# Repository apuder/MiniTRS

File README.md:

# MiniTRS

TBD

### Credits

* <a href="https://github.com/shaeberling/mini-trs">mini-trs</a> by Sascha H&auml;berling
* [Micro Model III](https://www.teamten.com/lawrence/projects/micro-model-3/) by Lawrence Kesteloot

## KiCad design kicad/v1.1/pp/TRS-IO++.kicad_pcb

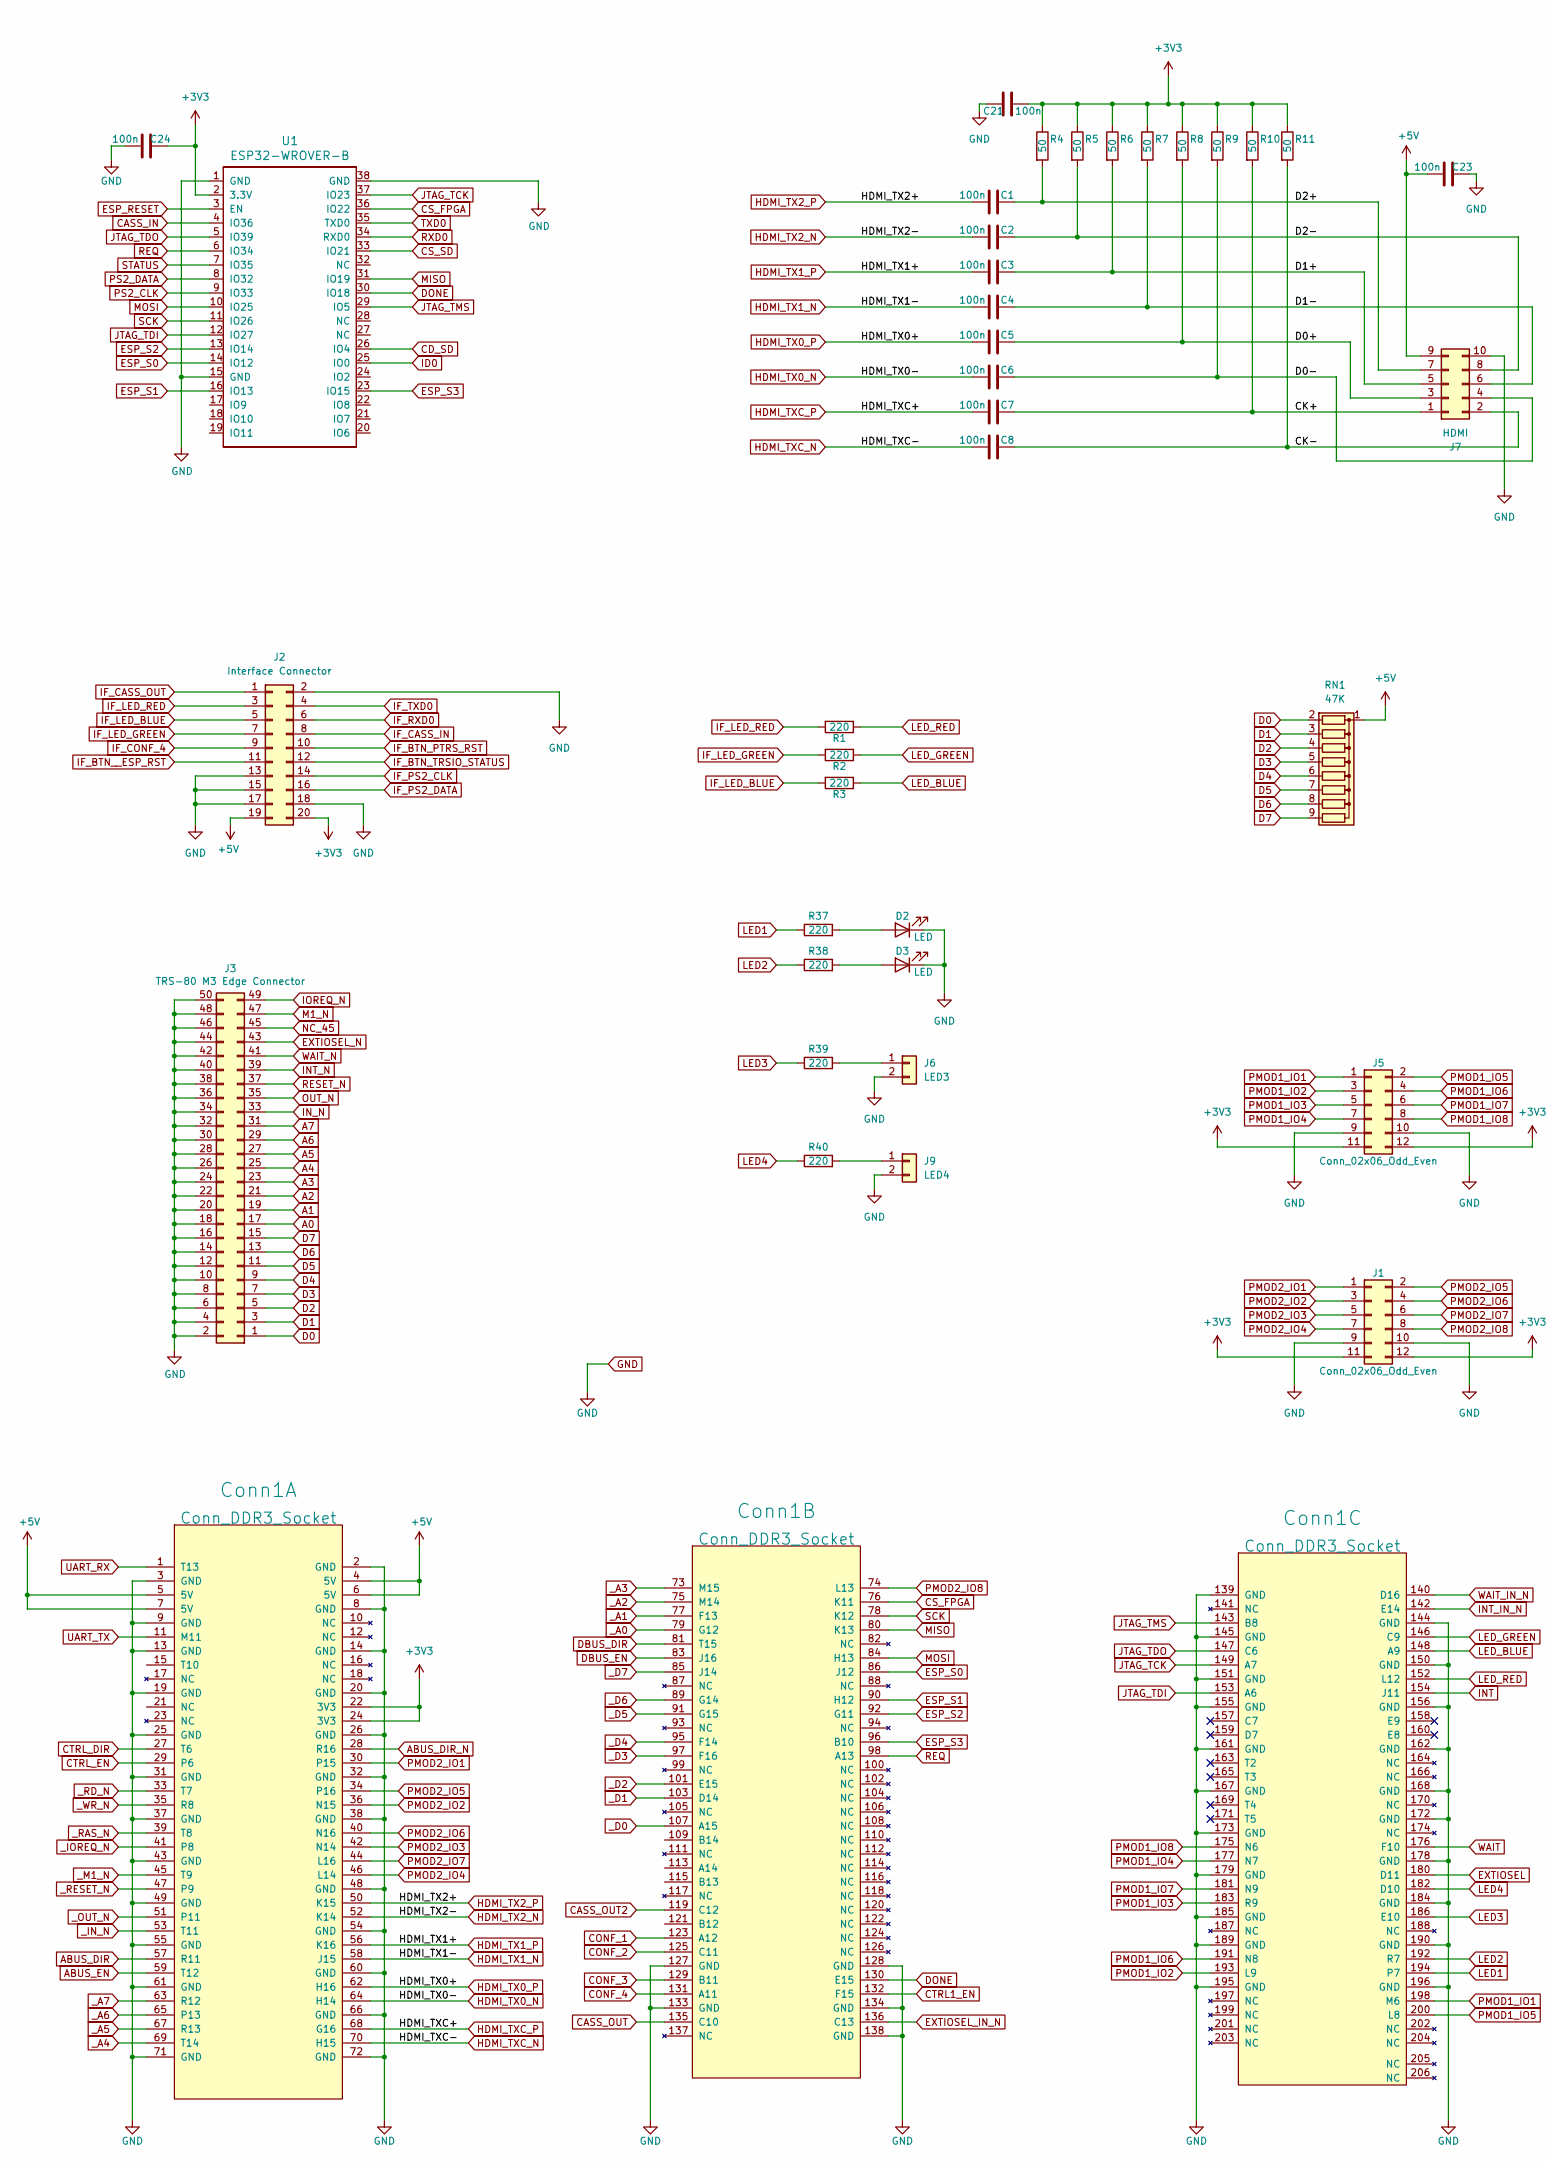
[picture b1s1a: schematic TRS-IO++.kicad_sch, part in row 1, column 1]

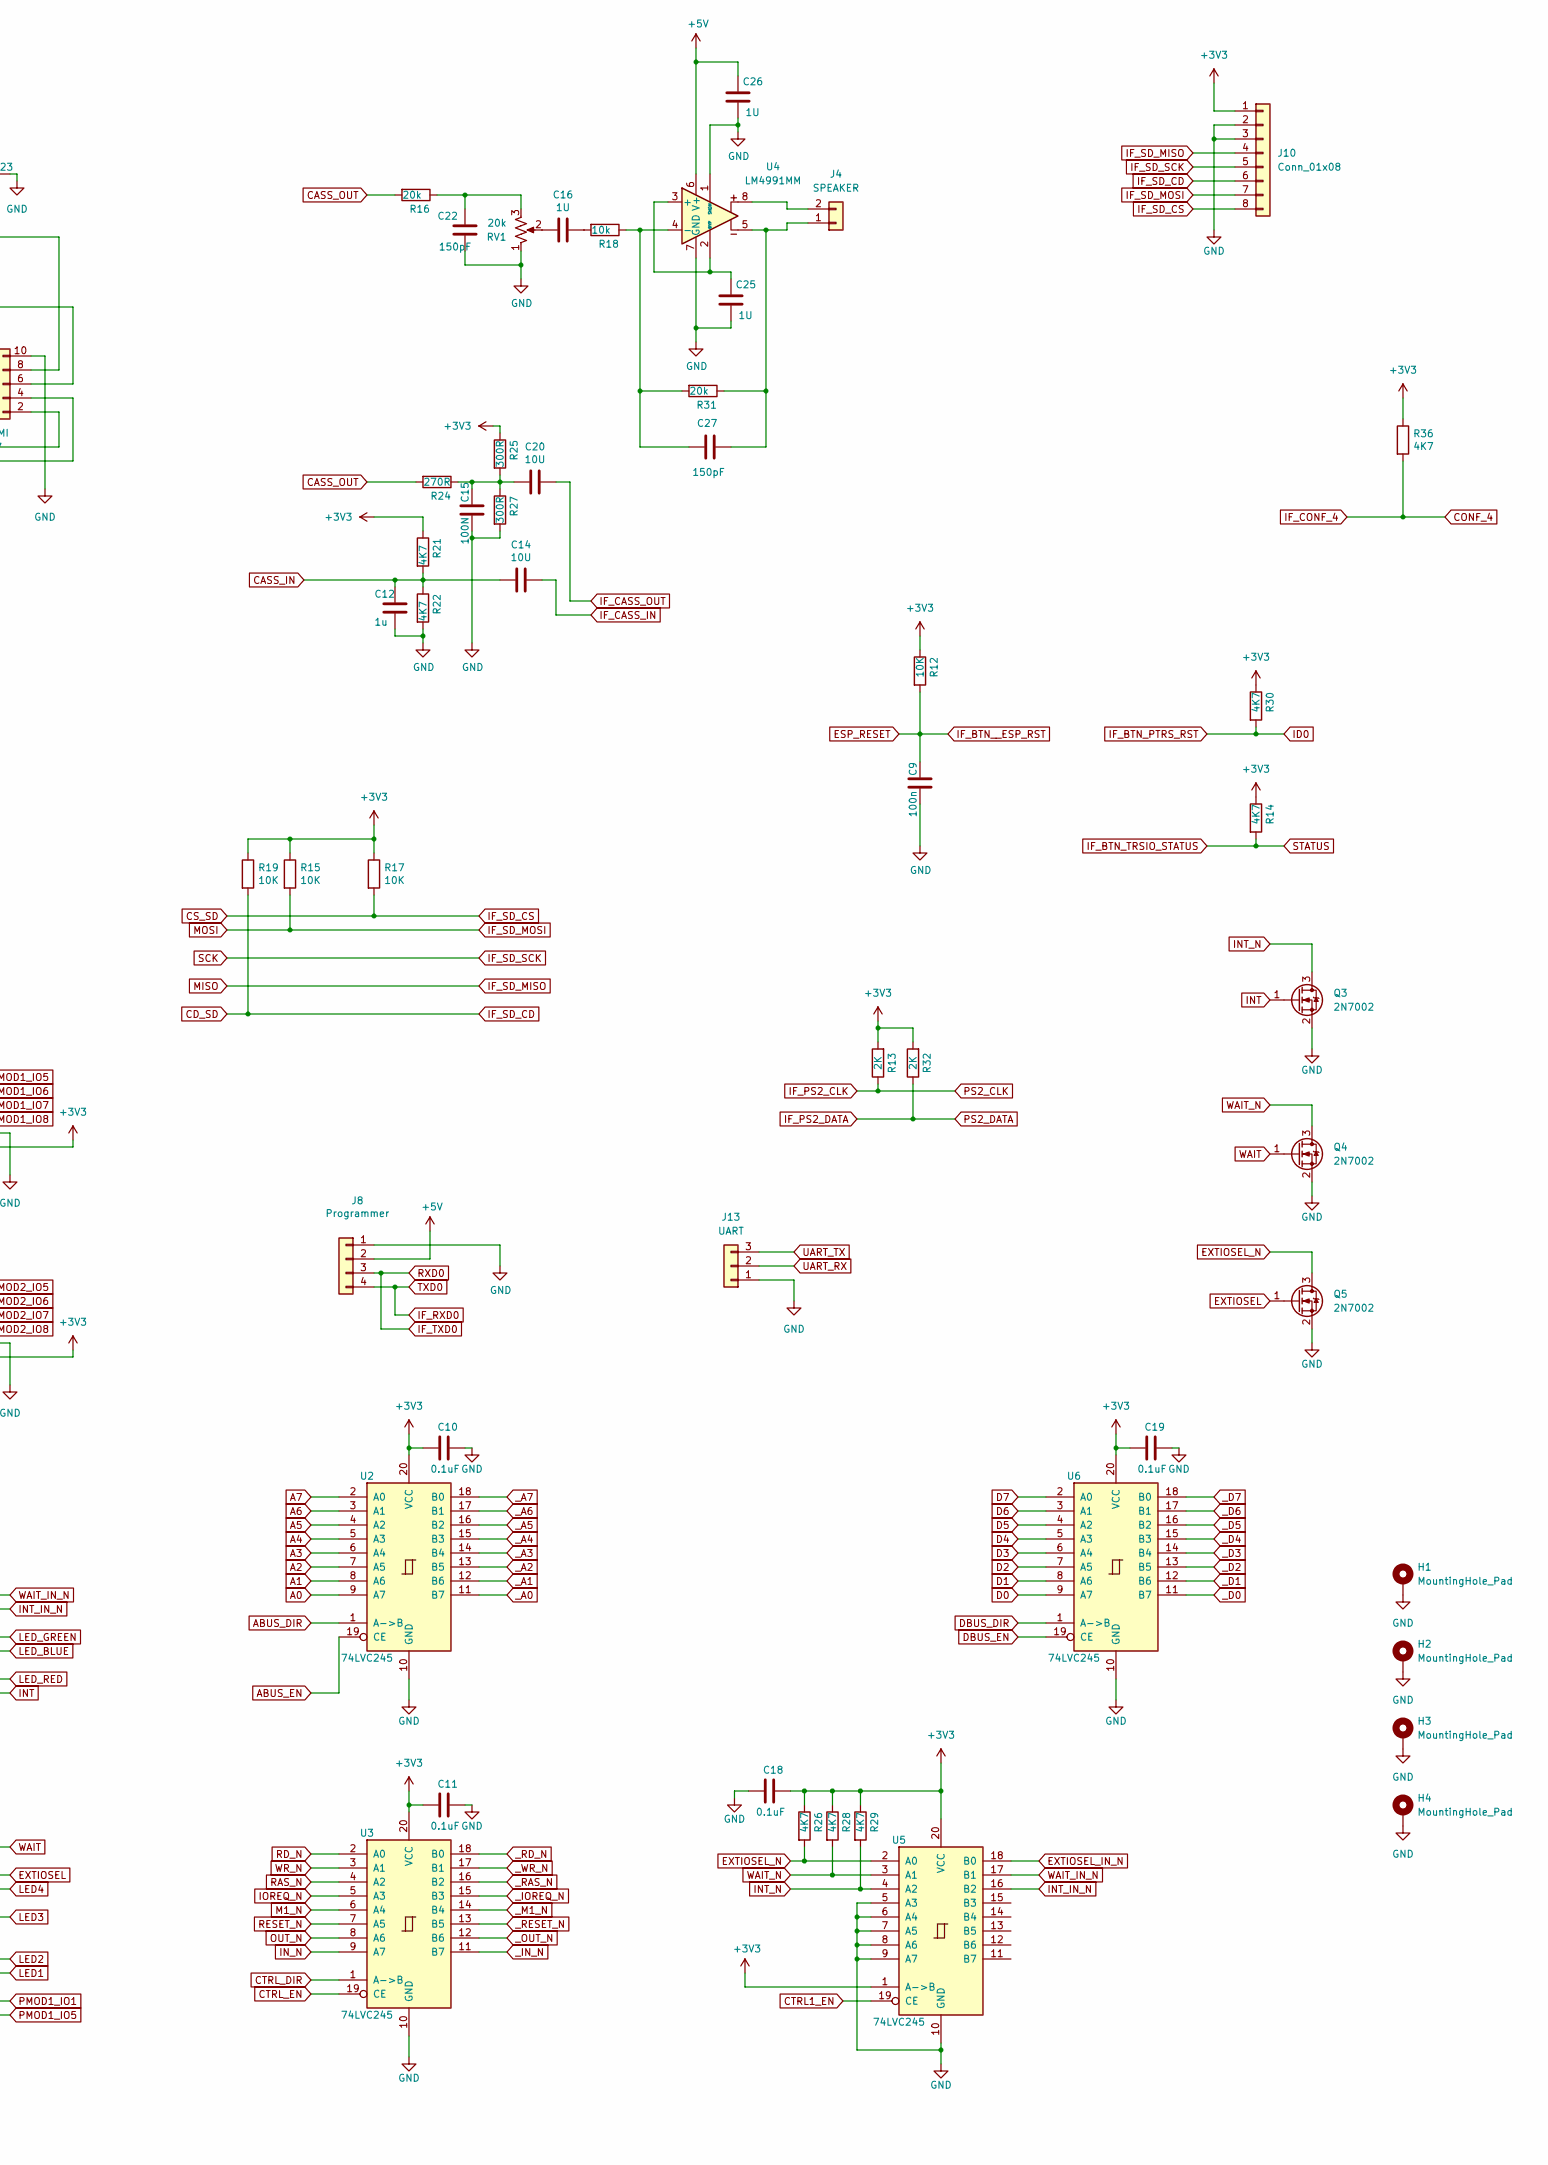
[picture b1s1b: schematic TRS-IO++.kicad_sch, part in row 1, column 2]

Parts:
C1, C2, C3, C4, C5, C6, C7, C8, C9, C21, C23, C24: 100n; C_0805_2012Metric_Pad1.18x1.45mm_HandSolder
C10, C11, C18, C19: 0.1uF; C_0805_2012Metric_Pad1.18x1.45mm_HandSolder
C12: 1u; C_1206_3216Metric_Pad1.33x1.80mm_HandSolder
C14, C20: 10U; C_1206_3216Metric_Pad1.33x1.80mm_HandSolder
C15: 100N; C_0805_2012Metric_Pad1.18x1.45mm_HandSolder
C16, C25, C26: 1U; C_0805_2012Metric_Pad1.18x1.45mm_HandSolder
C22, C27: 150pF; C_0805_2012Metric_Pad1.18x1.45mm_HandSolder
Conn1: Conn_DDR3_Socket; DDR3_socket; LCSC C306045
D2: LED; LED_0805_2012Metric_Pad1.15x1.40mm_HandSolder; LCSC C84256
D3: LED; LED_0805_2012Metric_Pad1.15x1.40mm_HandSolder
H1, H2, H3, H4: MountingHole_Pad; MountingHole_3mm_Pad_Via
J1, J5: Conn_02x06_Odd_Even; PinSocket_2x06_P2.54mm_Vertical; LCSC C358728
J2: Interface Connector; PinHeader_2x10_P1.27mm_Vertical; LCSC C3324132
J3: TRS-80 M3 Edge Connector; EDGE50
J4: SPEAKER; PinHeader_1x02_P2.54mm_Horizontal; LCSC C492410
J6: LED3; PinHeader_1x02_P2.54mm_Vertical; LCSC C225477
J7: HDMI; PinHeader_2x05_P1.27mm_Vertical_SMD; LCSC C598540
J8: Programmer; PinHeader_1x04_P2.54mm_Vertical; LCSC C2691448
J9: LED4; PinHeader_1x02_P2.54mm_Vertical; LCSC C225477
J10: Conn_01x08; PinHeader_1x08_P2.54mm_Vertical
J13: UART; PinHeader_1x03_P2.54mm_Vertical; LCSC C2937625
Q3, Q4, Q5: 2N7002; SOT-23
R1, R2, R3, R37, R38, R39, R40: 220; R_0805_2012Metric_Pad1.20x1.40mm_HandSolder
R4, R5, R6, R7, R8, R9, R10, R11: 50; R_0805_2012Metric_Pad1.20x1.40mm_HandSolder
R12, R15, R17, R19: 10K; R_0805_2012Metric_Pad1.20x1.40mm_HandSolder
R13, R32: 2K; R_0805_2012Metric_Pad1.20x1.40mm_HandSolder
R14, R21, R22, R26, R28, R29, R30, R36: 4K7; R_0805_2012Metric_Pad1.20x1.40mm_HandSolder
R16, R31: 20k; R_0805_2012Metric_Pad1.20x1.40mm_HandSolder
R18: 10k; R_0805_2012Metric_Pad1.20x1.40mm_HandSolder
R24: 270R; R_0805_2012Metric_Pad1.20x1.40mm_HandSolder
R25, R27: 300R; R_0805_2012Metric_Pad1.20x1.40mm_HandSolder
RN1: 47K; R_Array_SIP9; LCSC C61263
RV1: 20k; Potentiometer_Bourns_3266W_Vertical; LCSC C123864
U1: ESP32-WROVER-B; ESP32-WROVER
U2, U3, U5, U6: 74LVC245; SSOP-20_5.3x7.2mm_P0.65mm_slim; LCSC C393617
U4: LM4991MM; SOIC-8_3.9x4.9mm_P1.27mm; LCSC C2865568

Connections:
+3V3: C10.2, C11.2, C18.1, C19.2, C21.1, C24.2, Conn1.22 (3V3), Conn1.24 (3V3), J1.11, J1.12, J2.20, J5.11, J5.12, J10.1, R4.1, R5.1, R6.1, R7.1, R8.1, R9.1, R10.1, R11.1, R12.1, R13.2, R14.1, R15.1, R17.1, R19.1, R21.1, R25.1, R26.1, R28.1, R29.1, R30.1, R32.2, R36.1, U1.2 (3.3V), U2.20 (VCC), U3.20 (VCC), U5.1 (A->B), U5.20 (VCC), U6.20 (VCC)
+5V: C23.1, C26.1, Conn1.4 (5V), Conn1.5 (5V), Conn1.6 (5V), Conn1.7 (5V), J2.19, J7.9, J8.2, RN1.1 (common), U4.6 (V+)
/CK+: C7.2, J7.1, R10.2
/CK-: C8.2, J7.2, R11.2
/D0+: C5.2, J7.3, R8.2
/D0-: C6.2, J7.4, R9.2
/D1+: C3.2, J7.5, R6.2
/D1-: C4.2, J7.6, R7.2
/D2+: C1.2, J7.7, R4.2
/D2-: C2.2, J7.8, R5.2
A0: J3.17, U2.9 (A7)
A1: J3.19, U2.8 (A6)
A2: J3.21, U2.7 (A5)
A3: J3.23, U2.6 (A4)
A4: J3.25, U2.5 (A3)
A5: J3.27, U2.4 (A2)
A6: J3.29, U2.3 (A1)
A7: J3.31, U2.2 (A0)
ABUS_DIR: Conn1.57 (R11), U2.1 (A->B)
ABUS_DIR_N: Conn1.28 (R16)
ABUS_EN: Conn1.59 (T12), U2.19 (CE)
CASS_IN: C12.1, C14.2, R21.2, R22.1, U1.4 (IO36)
CASS_OUT: Conn1.135 (C10), R16.2, R24.2
CASS_OUT2: Conn1.119 (C12)
CD_SD: J10.6, R19.2, U1.26 (IO4)
CONF_1: Conn1.123 (A12)
CONF_2: Conn1.125 (C11)
CONF_3: Conn1.129 (B11)
CONF_4: Conn1.131 (A11), J2.9, R36.2
CS_FPGA: Conn1.76 (K11), U1.36 (IO22)
CS_SD: J10.8, R17.2, U1.33 (IO21)
CTRL1_EN: Conn1.132 (F15), U5.19 (CE)
CTRL_DIR: Conn1.27 (T6), U3.1 (A->B)
CTRL_EN: Conn1.29 (P6), U3.19 (CE)
D0: J3.1, RN1.2 (R1), U6.9 (A7)
D1: J3.3, RN1.3 (R2), U6.8 (A6)
D2: J3.5, RN1.4 (R3), U6.7 (A5)
D3: J3.7, RN1.5 (R4), U6.6 (A4)
D4: J3.9, RN1.6 (R5), U6.5 (A3)
D5: J3.11, RN1.7 (R6), U6.4 (A2)
D6: J3.13, RN1.8 (R7), U6.3 (A1)
D7: J3.15, RN1.9 (R8), U6.2 (A0)
DBUS_DIR: Conn1.81 (T15), U6.1 (A->B)
DBUS_EN: Conn1.83 (J16), U6.19 (CE)
DONE: Conn1.130 (E15), U1.30 (IO18)
ESP_RESET: C9.2, J2.11, R12.2, U1.3 (EN)
ESP_S0: Conn1.86 (J12), U1.14 (IO12)
ESP_S1: Conn1.90 (H12), U1.16 (IO13)
ESP_S2: Conn1.92 (G11), U1.13 (IO14)
ESP_S3: Conn1.96 (B10), U1.23 (IO15)
EXTIOSEL: Conn1.180 (D11), Q5.1 (G)
EXTIOSEL_IN_N: Conn1.136 (C13), U5.18 (B0)
EXTIOSEL_N: J3.43, Q5.3 (D), R26.2, U5.2 (A0)
GND: C9.1, C10.1, C11.1, C12.2, C15.2, C18.2, C19.1, C21.2, C22.2, C23.2, C24.1, C25.2, C26.2, Conn1.2 (GND), Conn1.3 (GND), Conn1.8 (GND), Conn1.9 (GND), Conn1.13 (GND), Conn1.14 (GND), Conn1.19 (GND), Conn1.20 (GND), Conn1.25 (GND), Conn1.26 (GND), Conn1.31 (GND), Conn1.32 (GND), Conn1.37 (GND), Conn1.38 (GND), Conn1.43 (GND), Conn1.48 (GND), Conn1.49 (GND), Conn1.54 (GND), Conn1.55 (GND), Conn1.60 (GND), Conn1.61 (GND), Conn1.66 (GND), Conn1.71 (GND), Conn1.72 (GND), Conn1.127 (GND), Conn1.128 (GND), Conn1.133 (GND), Conn1.134 (GND), Conn1.138 (GND), Conn1.139 (GND), Conn1.144 (GND), Conn1.145 (GND), Conn1.150 (GND), Conn1.151 (GND), Conn1.155 (GND), Conn1.156 (GND), Conn1.161 (GND), Conn1.162 (GND), Conn1.167 (GND), Conn1.168 (GND), Conn1.172 (GND), Conn1.173 (GND), Conn1.178 (GND), Conn1.179 (GND), Conn1.184 (GND), Conn1.185 (GND), Conn1.189 (GND), Conn1.190 (GND), Conn1.195 (GND), Conn1.196 (GND), D2.1 (K), D3.1 (K), H1.1, H2.1, H3.1, H4.1, J1.9, J1.10, J2.2, J2.13, J2.15, J2.17, J2.18, J3.2, J3.4, J3.6, J3.8, J3.10, J3.12, J3.14, J3.16, J3.18, J3.20, J3.22, J3.24, J3.26, J3.28, J3.30, J3.32, J3.34, J3.36, J3.38, J3.40, J3.42, J3.44, J3.46, J3.48, J3.50, J5.9, J5.10, J6.2, J7.10, J8.1, J9.2, J10.2, J10.3, J13.1, Q3.2 (S), Q4.2 (S), Q5.2 (S), R22.2, R27.2, RV1.1, U1.1 (GND), U1.15 (GND), U1.38 (GND), U2.10 (GND), U3.10 (GND), U4.1 (SHDN), U4.7 (GND), U5.5 (A3), U5.6 (A4), U5.7 (A5), U5.8 (A6), U5.9 (A7), U5.10 (GND), U6.10 (GND)
HDMI_TX0_N: C6.1, Conn1.64 (H14)
HDMI_TX0_P: C5.1, Conn1.62 (H16)
HDMI_TX1_N: C4.1, Conn1.58 (J15)
HDMI_TX1_P: C3.1, Conn1.56 (K16)
HDMI_TX2_N: C2.1, Conn1.52 (K14)
HDMI_TX2_P: C1.1, Conn1.50 (K15)
HDMI_TXC_N: C8.1, Conn1.70 (H15)
HDMI_TXC_P: C7.1, Conn1.68 (G16)
ID0: J2.10, R30.2, U1.25 (IO0)
IF_BTN_TRSIO_STATUS: J2.12, R14.2, U1.7 (IO35)
IF_CASS_IN: C14.1, J2.8
IF_CASS_OUT: C20.1, J2.1
IF_LED_BLUE: J2.5, R3.2
IF_LED_GREEN: J2.7, R2.2
IF_LED_RED: J2.3, R1.2
IF_PS2_CLK: J2.14, R13.1, U1.9 (IO33)
IF_PS2_DATA: J2.16, R32.1, U1.8 (IO32)
IF_RXD0: J2.6, J8.4, U1.35 (TXD0)
IF_SD_MISO: Conn1.80 (K13), J10.4, U1.31 (IO19)
IF_SD_MOSI: Conn1.84 (H13), J10.7, R15.2, U1.10 (IO25)
IF_SD_SCK: Conn1.78 (K12), J10.5, U1.11 (IO26)
IF_TXD0: J2.4, J8.3, U1.34 (RXD0)
INT: Conn1.154 (J11), Q3.1 (G)
INT_IN_N: Conn1.142 (E14), U5.16 (B2)
INT_N: J3.39, Q3.3 (D), R29.2, U5.4 (A2)
IN_N: J3.33, U3.9 (A7)
IOREQ_N: J3.49, U3.5 (A3)
JTAG_TCK: Conn1.149 (A7), U1.37 (IO23)
JTAG_TDI: Conn1.153 (A6), U1.12 (IO27)
JTAG_TDO: Conn1.147 (C6), U1.5 (IO39)
JTAG_TMS: Conn1.143 (B8), U1.29 (IO5)
LED1: Conn1.194 (P7), R37.1
LED2: Conn1.192 (R7), R38.1
LED3: Conn1.186 (E10), R39.1
LED4: Conn1.182 (D10), R40.1
LED_BLUE: Conn1.148 (A9), R3.1
LED_GREEN: Conn1.146 (C9), R2.1
LED_RED: Conn1.152 (L12), R1.1
M1_N: J3.47, U3.6 (A4)
NC_45: J3.45
unnamed: C15.1, C20.2, R24.1, R25.2, R27.1
unnamed: C16.1, R18.2
unnamed: C16.2, RV1.2
unnamed: C22.1, R16.1, RV1.3
unnamed: D2.2 (A), R37.2
unnamed: D3.2 (A), R38.2
unnamed: C27.1, J4.1, R31.1, U4.5
unnamed: J4.2, U4.8
unnamed: J6.1, R39.2
unnamed: J9.1, R40.2
unnamed: C25.1, U4.2 (BYP), U4.3 (+)
unnamed: C27.2, R18.1, R31.2, U4.4 (-)
OUT_N: J3.35, U3.8 (A6)
PMOD1_IO1: Conn1.198 (M6), J5.1
PMOD1_IO2: Conn1.193 (L9), J5.3
PMOD1_IO3: Conn1.183 (R9), J5.5
PMOD1_IO4: Conn1.177 (N7), J5.7
PMOD1_IO5: Conn1.200 (L8), J5.2
PMOD1_IO6: Conn1.191 (N8), J5.4
PMOD1_IO7: Conn1.181 (N9), J5.6
PMOD1_IO8: Conn1.175 (N6), J5.8
PMOD2_IO1: Conn1.30 (P15), J1.1
PMOD2_IO2: Conn1.36 (N15), J1.3
PMOD2_IO3: Conn1.42 (N14), J1.5
PMOD2_IO4: Conn1.46 (L14), J1.7
PMOD2_IO5: Conn1.34 (P16), J1.2
PMOD2_IO6: Conn1.40 (N16), J1.4
PMOD2_IO7: Conn1.44 (L16), J1.6
PMOD2_IO8: Conn1.74 (L13), J1.8
RAS_N: U3.4 (A2)
RD_N: U3.2 (A0)
REQ: Conn1.98 (A13), U1.6 (IO34)
RESET_N: J3.37, U3.7 (A5)
UART_RX: Conn1.1 (T13), J13.2
UART_TX: Conn1.11 (M11), J13.3
WAIT: Conn1.176 (F10), Q4.1 (G)
WAIT_IN_N: Conn1.140 (D16), U5.17 (B1)
WAIT_N: J3.41, Q4.3 (D), R28.2, U5.3 (A1)
WR_N: U3.3 (A1)
_A0: Conn1.79 (G12), U2.11 (B7)
_A1: Conn1.77 (F13), U2.12 (B6)
_A2: Conn1.75 (M14), U2.13 (B5)
_A3: Conn1.73 (M15), U2.14 (B4)
_A4: Conn1.69 (T14), U2.15 (B3)
_A5: Conn1.67 (R13), U2.16 (B2)
_A6: Conn1.65 (P13), U2.17 (B1)
_A7: Conn1.63 (R12), U2.18 (B0)
_D0: Conn1.107 (A15), U6.11 (B7)
_D1: Conn1.103 (D14), U6.12 (B6)
_D2: Conn1.101 (E15), U6.13 (B5)
_D3: Conn1.97 (F16), U6.14 (B4)
_D4: Conn1.95 (F14), U6.15 (B3)
_D5: Conn1.91 (G15), U6.16 (B2)
_D6: Conn1.89 (G14), U6.17 (B1)
_D7: Conn1.85 (J14), U6.18 (B0)
_IN_N: Conn1.53 (T11), U3.11 (B7)
_IOREQ_N: Conn1.41 (P8), U3.15 (B3)
_M1_N: Conn1.45 (T9), U3.14 (B4)
_OUT_N: Conn1.51 (P11), U3.12 (B6)
_RAS_N: Conn1.39 (T8), U3.16 (B2)
_RD_N: Conn1.33 (T7), U3.18 (B0)
_RESET_N: Conn1.47 (P9), U3.13 (B5)
_WR_N: Conn1.35 (R8), U3.17 (B1)

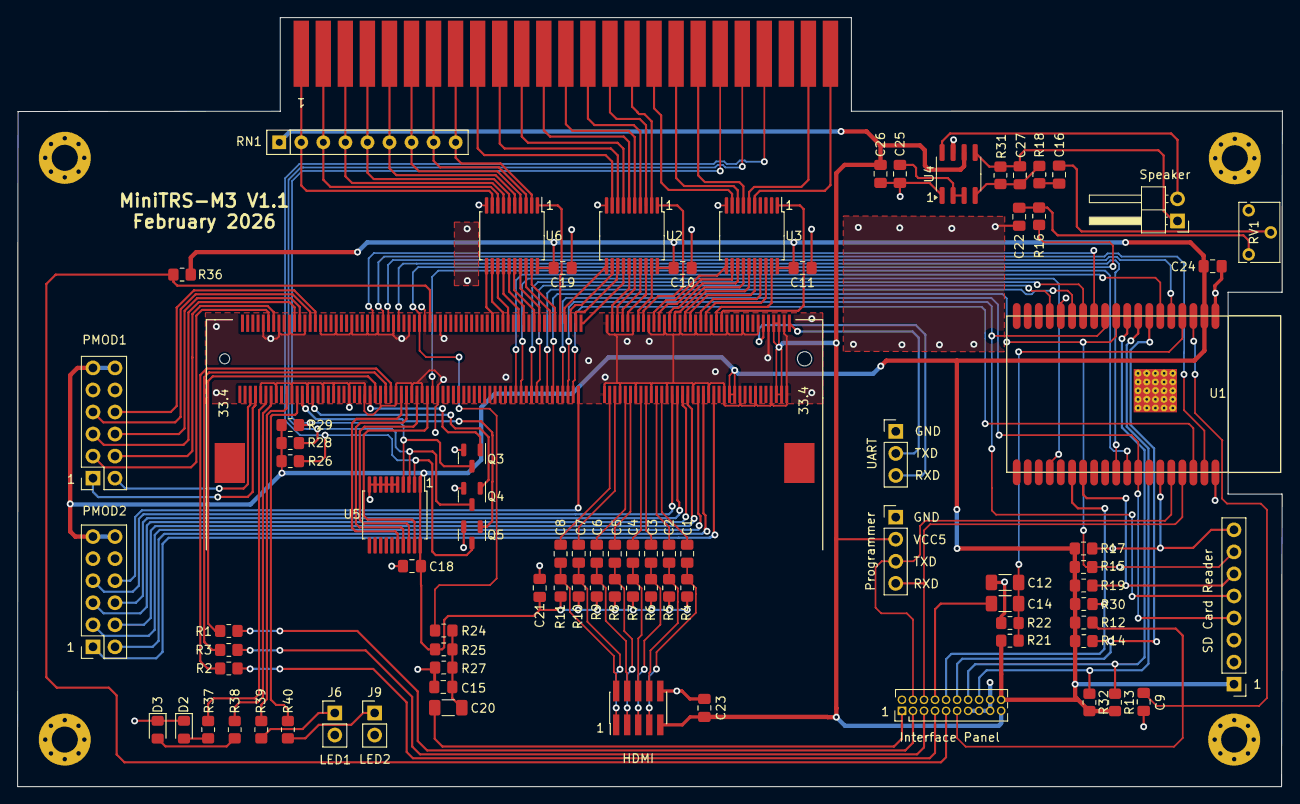
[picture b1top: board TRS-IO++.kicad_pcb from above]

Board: 2 copper layers, 145.7 x 88.6 mm, 89 parts (0 on the bottom side), 148 nets.
